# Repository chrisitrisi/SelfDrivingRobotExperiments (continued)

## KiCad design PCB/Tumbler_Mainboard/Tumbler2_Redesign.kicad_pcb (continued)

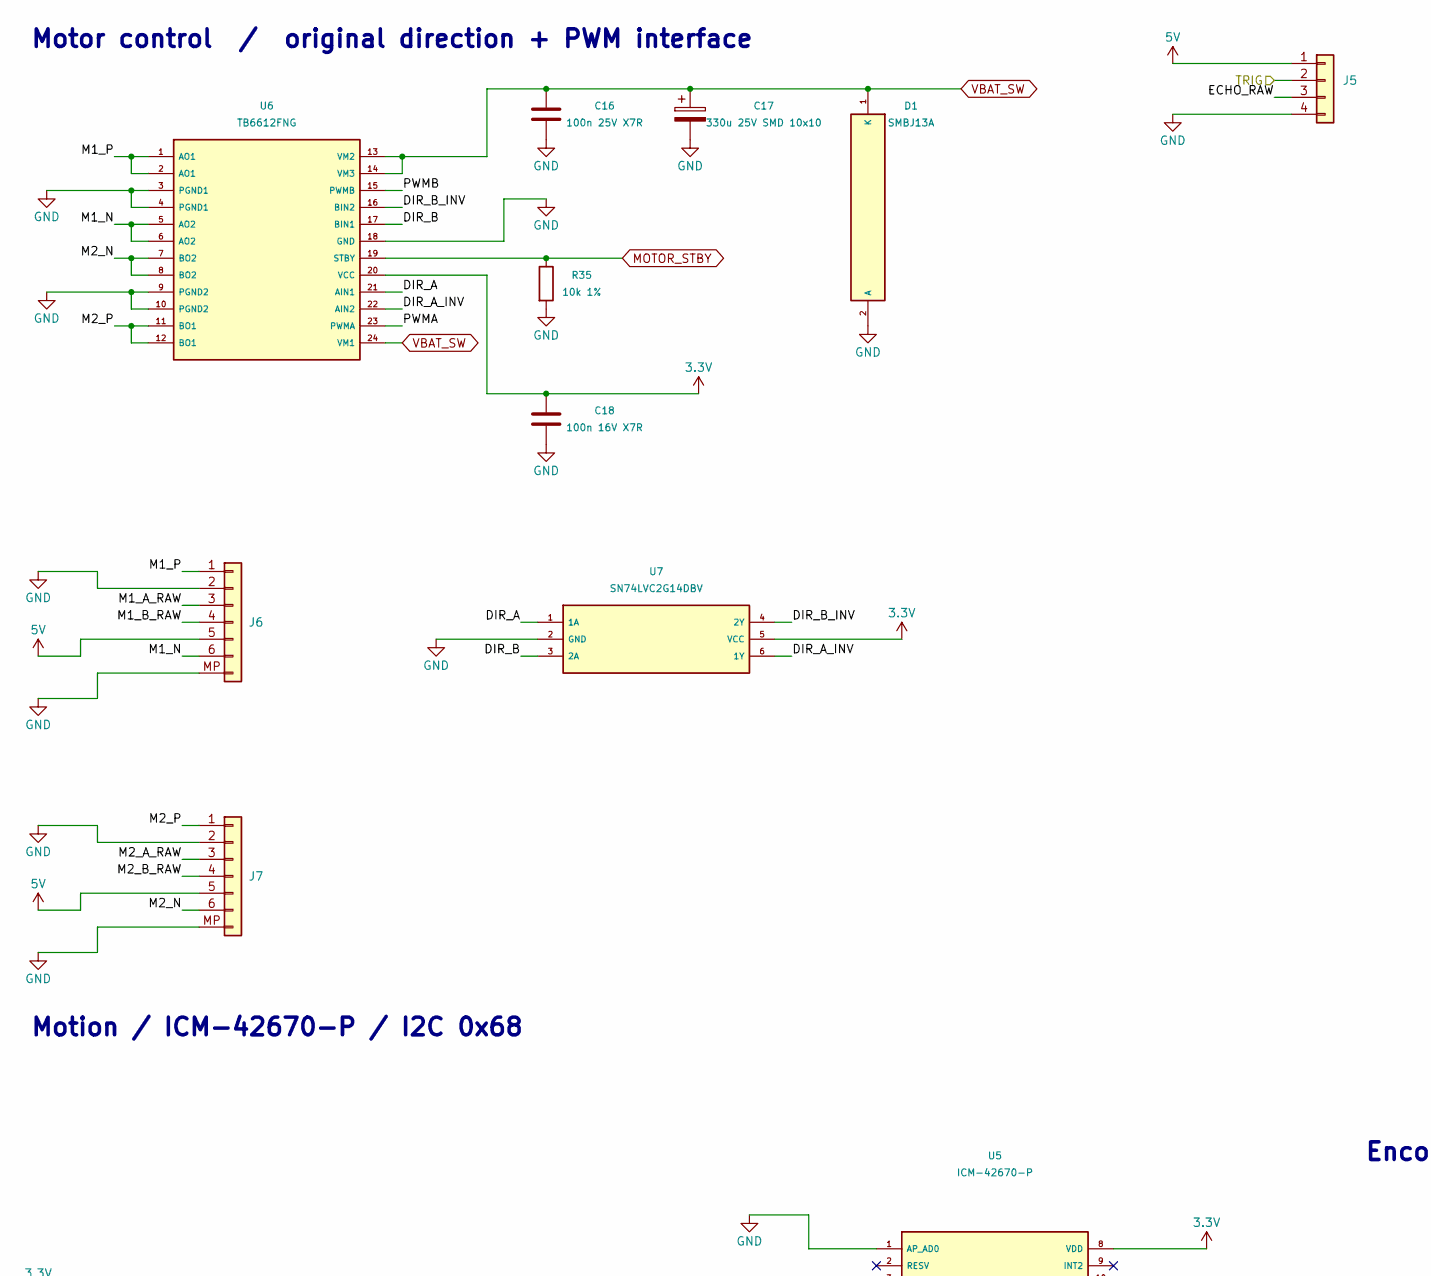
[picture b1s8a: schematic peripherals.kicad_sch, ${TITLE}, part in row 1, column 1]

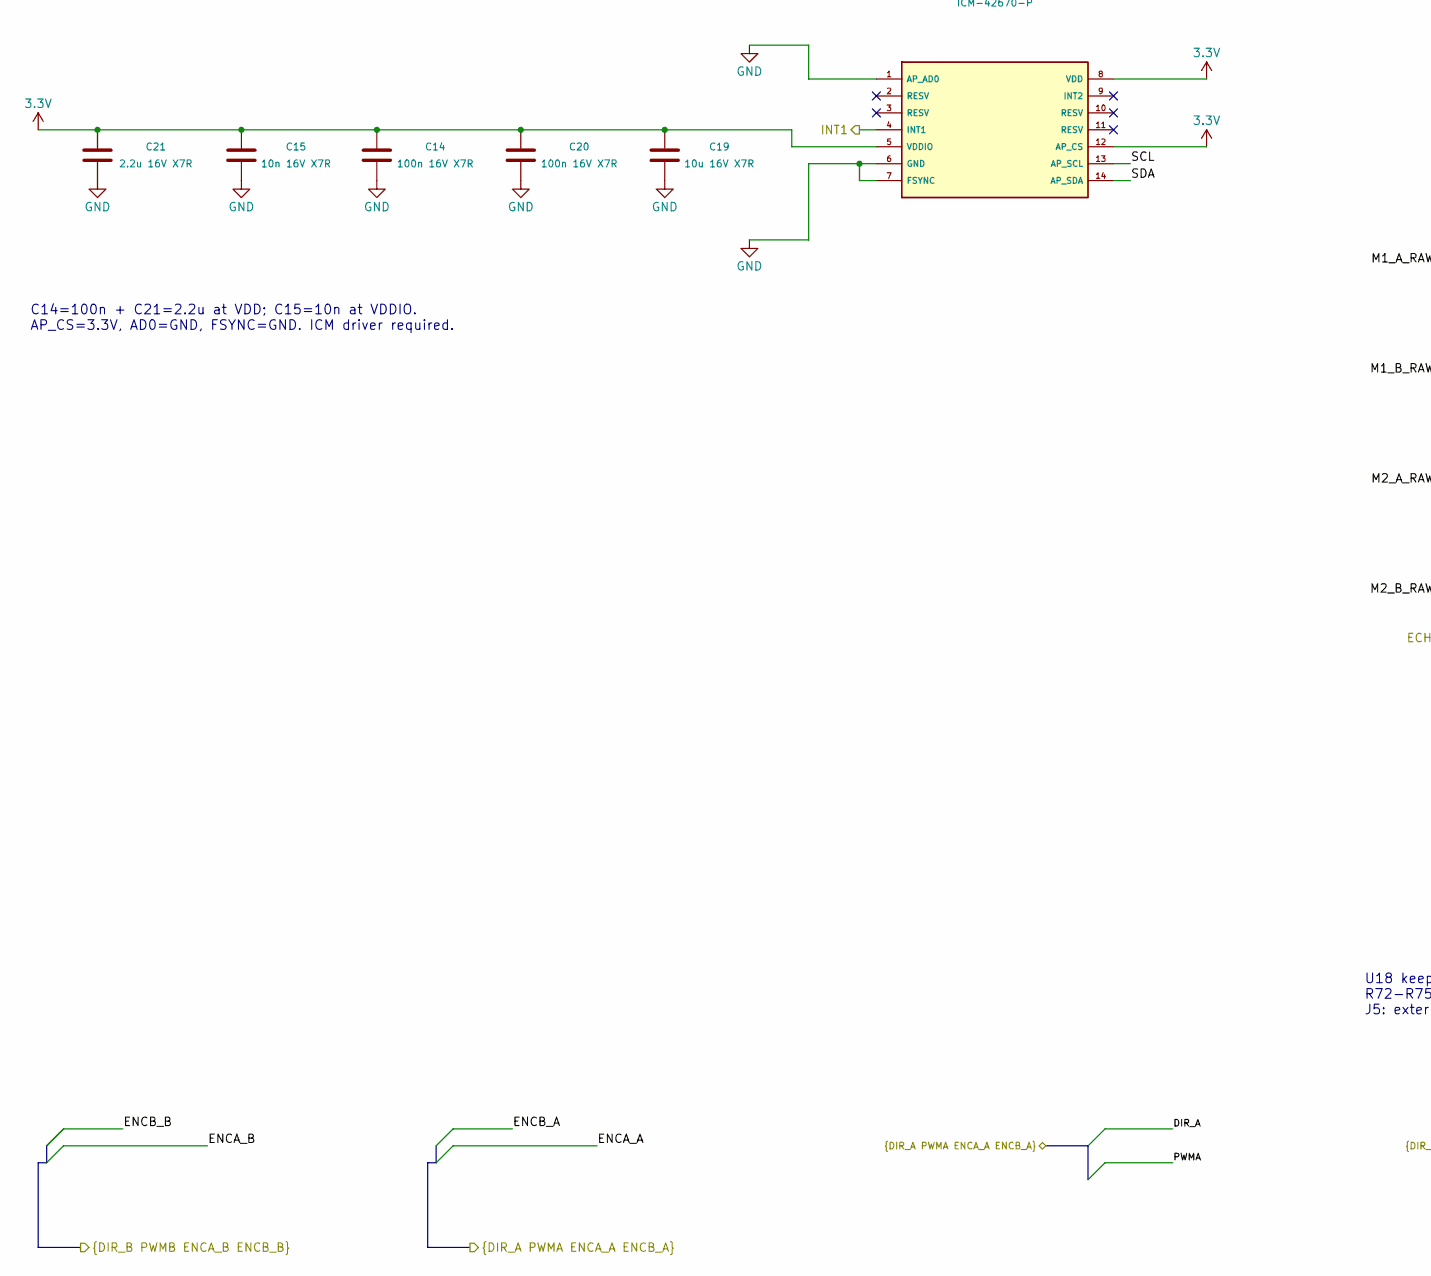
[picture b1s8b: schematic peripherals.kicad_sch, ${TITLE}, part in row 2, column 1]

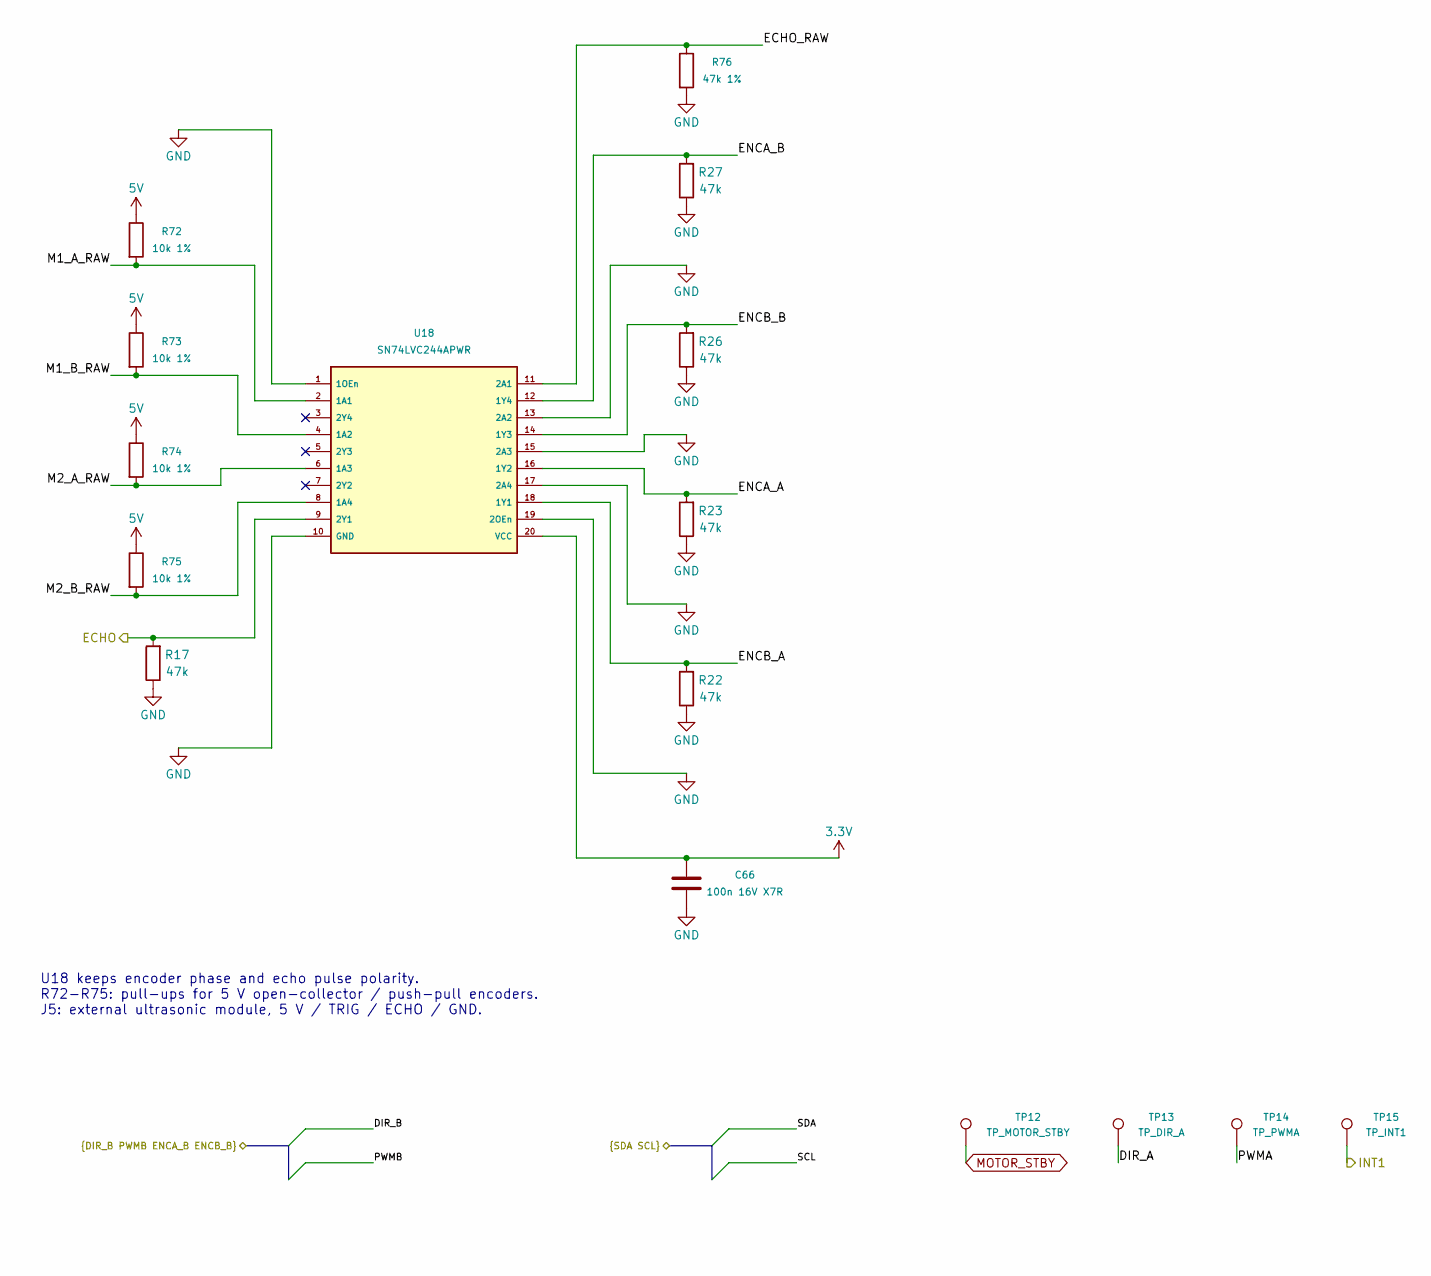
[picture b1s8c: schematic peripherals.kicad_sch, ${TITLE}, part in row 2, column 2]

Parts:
C14, C18, C20, C66: 100n 16V X7R; C_0603_1608Metric; LCSC PN C14663
C15: 10n 16V X7R; C_0603_1608Metric; LCSC PN C57112
C16: 100n 25V X7R; C_0603_1608Metric; LCSC PN C14663
C17: 330u 25V SMD 10x10; CP_Elec_10x10; LCSC PN C5632144
C19: 10u 16V X7R; C_0805_2012Metric; LCSC PN C95841
C21: 2.2u 16V X7R; C_0603_1608Metric; LCSC PN C6600149
D1: SMBJ13A; D_SMB; LCSC PN C353394
J5: Conn_01x04; PinHeader_1x04_P2.54mm_Vertical; LCSC PN C5116530
J6, J7: Conn_01x06; JST_XH_S6B-XH-SM4-TB_1x06-1MP_P2.50mm_Horizontal; LCSC PN C191914
R17, R22, R23, R26, R27: 47k; R_0603_1608Metric; LCSC PN C25819
R35, R72, R73, R74, R75: 10k 1%; R_0603_1608Metric; LCSC PN C25804
R76: 47k 1%; R_0603_1608Metric; LCSC PN C25819
TP12: TP_MOTOR_STBY; TestPoint_Pad_D1.0mm
TP13: TP_DIR_A; TestPoint_Pad_D1.0mm
TP14: TP_PWMA; TestPoint_Pad_D1.0mm
TP15: TP_INT1; TestPoint_Pad_D1.0mm
U5: ICM-42670-P; LGA-14_3x2.5mm_P0.5mm_LayoutBorder3x4y; LCSC PN C3288646
U6: TB6612FNG; SSOP-24_5.3x8.2mm_P0.65mm; LCSC PN C141517
U7: SN74LVC2G14DBV; SOT-23-6; LCSC PN C5375976
U18: SN74LVC244APWR; TSSOP-20_4.4x6.5mm_P0.65mm; LCSC PN C7668

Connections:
3.3V: C14.1, C15.1, C18.1, C19.1, C20.1, C21.1, C66.1, U5.5 (VDDIO), U5.8 (VDD), U5.12 (AP_CS), U6.20 (VCC), U7.5 (VCC), U18.20 (VCC); also elsewhere on the board
5V: J5.1, J6.5, J7.5, R72.1, R73.1, R74.1, R75.1; also elsewhere on the board
/LiDAR x8/SCL: U5.13 (AP_SCL); also elsewhere on the board
/LiDAR x8/SDA: U5.14 (AP_SDA); also elsewhere on the board
/MCU/DIR_A: TP13.1, U6.21 (AIN1), U7.1 (1A); also elsewhere on the board
/MCU/DIR_B: U6.17 (BIN1), U7.3 (2A); also elsewhere on the board
/MCU/ECHO: R17.2, U18.9 (2Y1); also elsewhere on the board
/MCU/ENCA_A: R23.2, U18.16 (1Y2); also elsewhere on the board
/MCU/ENCA_B: R27.2, U18.12 (1Y4); also elsewhere on the board
/MCU/ENCB_A: R22.2, U18.18 (1Y1); also elsewhere on the board
/MCU/ENCB_B: R26.2, U18.14 (1Y3); also elsewhere on the board
/MCU/INT1: TP15.1, U5.4 (INT1); also elsewhere on the board
/MCU/PWMA: TP14.1, U6.23 (PWMA); also elsewhere on the board
/MCU/PWMB: U6.15 (PWMB); also elsewhere on the board
/MCU/TRIG: J5.2; also elsewhere on the board
/Peripherals/DIR_A_INV: U6.22 (AIN2), U7.6 (1Y)
/Peripherals/DIR_B_INV: U6.16 (BIN2), U7.4 (2Y)
/Peripherals/ECHO_RAW: J5.3, R76.1, U18.11 (2A1)
/Peripherals/M1_A_RAW: J6.3, R72.2, U18.2 (1A1)
/Peripherals/M1_B_RAW: J6.4, R73.2, U18.4 (1A2)
/Peripherals/M1_N: J6.6, U6.5 (AO2), U6.6 (AO2)
/Peripherals/M1_P: J6.1, U6.1 (AO1), U6.2 (AO1)
/Peripherals/M2_A_RAW: J7.3, R74.2, U18.6 (1A3)
/Peripherals/M2_B_RAW: J7.4, R75.2, U18.8 (1A4)
/Peripherals/M2_N: J7.6, U6.7 (BO2), U6.8 (BO2)
/Peripherals/M2_P: J7.1, U6.11 (BO1), U6.12 (BO1)
GND: C14.2, C15.2, C16.2, C17.2, C18.2, C19.2, C20.2, C21.2, C66.2, D1.2 (A), J5.4, J6.2, J6.MP, J7.2, J7.MP, R17.1, R22.1, R23.1, R26.1, R27.1, R35.2, R76.2, U5.1 (AP_AD0), U5.6 (GND), U5.7 (FSYNC), U6.3 (PGND1), U6.4 (PGND1), U6.9 (PGND2), U6.10 (PGND2), U6.18 (GND), U7.2 (GND), U18.1 (1OEn), U18.10 (GND), U18.13 (2A2), U18.15 (2A3), U18.17 (2A4), U18.19 (2OEn); also elsewhere on the board
MOTOR_STBY: R35.1, TP12.1, U6.19 (STBY); also elsewhere on the board
VBAT_SW: C16.1, C17.1, D1.1 (K), U6.13 (VM2), U6.14 (VM3), U6.24 (VM1); also elsewhere on the board

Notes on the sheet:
Motor control / original direction + PWM interface
Encoder and echo inputs / 5 V to 3.3 V
Motion / ICM-42670-P / I2C 0x68
U18 keeps encoder phase and echo pulse polarity. R72-R75: pull-ups for 5 V open-collector / push-pull encoders. J5: external ultrasonic module, 5 V / TRIG / ECHO / GND.
C14=100n + C21=2.2u at VDD; C15=10n at VDDIO. AP_CS=3.3V, AD0=GND, FSYNC=GND. ICM driver required.

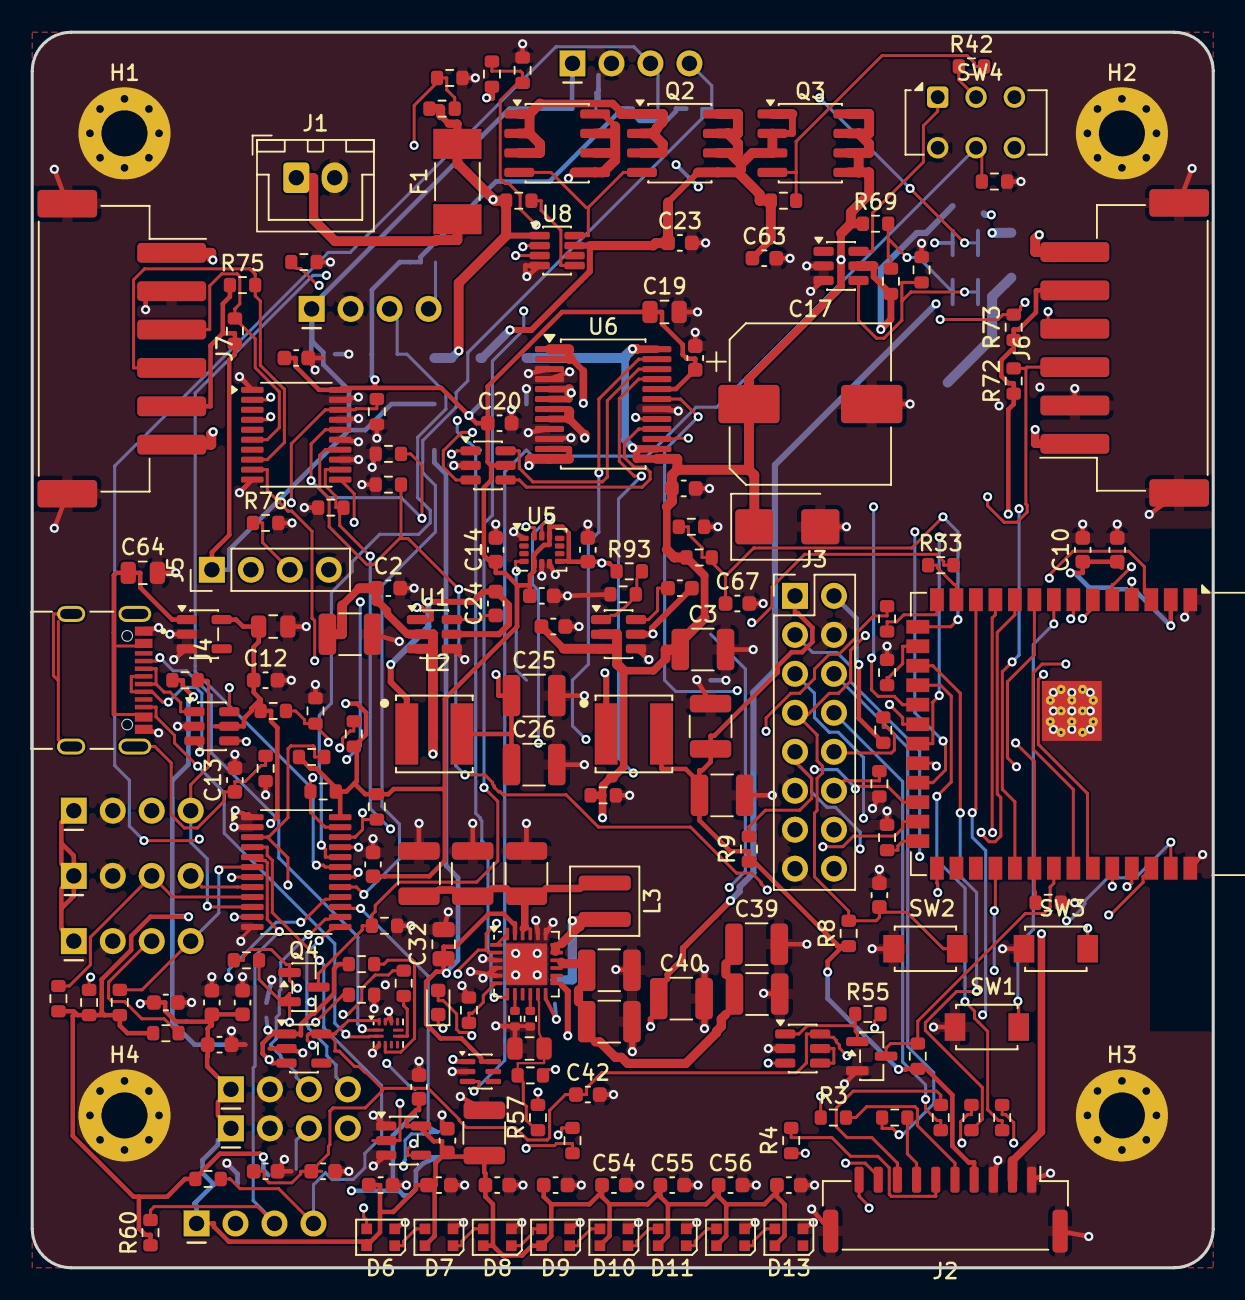
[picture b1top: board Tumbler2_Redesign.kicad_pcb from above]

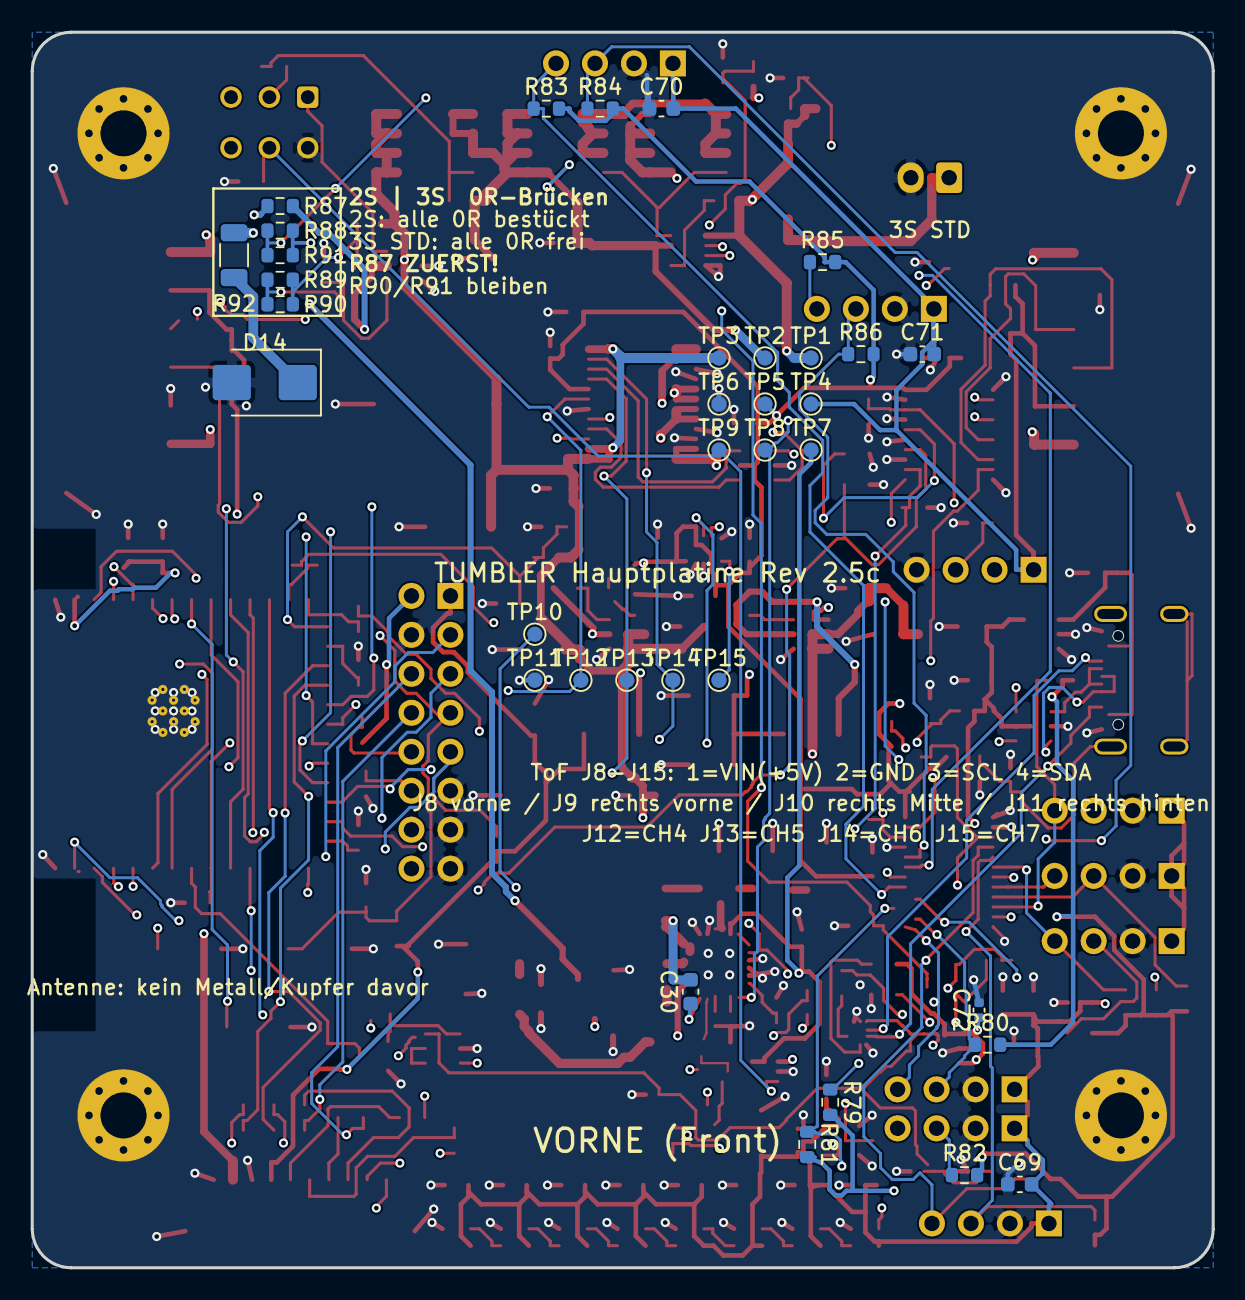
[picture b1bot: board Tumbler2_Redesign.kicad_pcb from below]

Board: 4 copper layers, 77.0 x 80.5 mm, 221 parts (35 on the bottom side), 133 nets.

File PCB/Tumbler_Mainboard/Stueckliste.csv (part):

Referenz;Wert / Bestelltyp;Footprint;Bestücken;Spezifikation / offene Freigabe;Datenblatt;LCSC (JLC, Stand 28.11.2026)
C1;22u 25V X7R;Capacitor_SMD:C_1210_3225Metric;Ja;"MLCC X7R; falls keine Spannung im Wert: >=16 V | Rev 2.5b: auf 22u/25V 1210 vereinheitlicht (eine JLC-Teilenummer weniger)";;C309062
C2;100n 25V X7R;Capacitor_SMD:C_0603_1608Metric;Ja;"MLCC X7R; falls keine Spannung im Wert: >=16 V";;C14663
C3;22u 25V X7R;Capacitor_SMD:C_1210_3225Metric;Ja;"MLCC X7R; falls keine Spannung im Wert: >=16 V | Rev 2.5b: auf 22u/25V 1210 vereinheitlicht (eine JLC-Teilenummer weniger)";;C309062
C4;100n 25V X7R;Capacitor_SMD:C_0603_1608Metric;Ja;"MLCC X7R; falls keine Spannung im Wert: >=16 V";;C14663
C6;22u 25V X7R;Capacitor_SMD:C_1210_3225Metric;Ja;"MLCC X7R; falls keine Spannung im Wert: >=16 V | Rev 2.5b: auf 22u/25V 1210 vereinheitlicht (eine JLC-Teilenummer weniger)";;C309062
C7;22u 25V X7R;Capacitor_SMD:C_1210_3225Metric;Ja;"MLCC X7R; falls keine Spannung im Wert: >=16 V | Rev 2.5b: auf 22u/25V 1210 vereinheitlicht (eine JLC-Teilenummer weniger)";;C309062
C8;100n 25V X7R;Capacitor_SMD:C_0603_1608Metric;Ja;"MLCC X7R; falls keine Spannung im Wert: >=16 V";;C14663
C9;10u 25V X5R;Capacitor_SMD:C_0603_1608Metric;Ja;MLCC X5R, 25 V, an 3,3 V;;C96446
C10;100nF;Capacitor_SMD:C_0603_1608Metric;Ja;"MLCC X7R; falls keine Spannung im Wert: >=16 V";;C14663
C11;1uF;Capacitor_SMD:C_0603_1608Metric;Ja;"MLCC X7R; falls keine Spannung im Wert: >=16 V";;C59782
C12;100nF;Capacitor_SMD:C_0603_1608Metric;Ja;"MLCC X7R; falls keine Spannung im Wert: >=16 V";;C14663
C13;100nF;Capacitor_SMD:C_0603_1608Metric;Ja;"MLCC X7R; falls keine Spannung im Wert: >=16 V";;C14663
C14;100n 16V X7R;Capacitor_SMD:C_0603_1608Metric;Ja;"MLCC X7R; falls keine Spannung im Wert: >=16 V";;C14663
C15;10n 16V X7R;Capacitor_SMD:C_0603_1608Metric;Ja;"MLCC X7R; falls keine Spannung im Wert: >=16 V";;C57112
C16;100n 25V X7R;Capacitor_SMD:C_0603_1608Metric;Ja;"MLCC X7R; falls keine Spannung im Wert: >=16 V";;C14663
C17;330u 25V SMD 10x10;Capacitor_SMD:CP_Elec_10x10;Ja;Rev 2.5b: SamYoung CLU25V330M10*10 (330 uF/25 V, 10x10 SMD, bei JLC lagernd);;C5632144
C18;100n 16V X7R;Capacitor_SMD:C_0603_1608Metric;Ja;"MLCC X7R; falls keine Spannung im Wert: >=16 V";;C14663
C19;10u 16V X7R;Capacitor_SMD:C_0805_2012Metric;Ja;"MLCC X7R; falls keine Spannung im Wert: >=16 V";;C95841
C20;100n 16V X7R;Capacitor_SMD:C_0603_1608Metric;Ja;"MLCC X7R; falls keine Spannung im Wert: >=16 V";;C14663
C21;2.2u 16V X7R;Capacitor_SMD:C_0603_1608Metric;Ja;"MLCC X7R; falls keine Spannung im Wert: >=16 V";;C6600149
C23;100n 25V X7R;Capacitor_SMD:C_0603_1608Metric;Ja;"MLCC X7R; falls keine Spannung im Wert: >=16 V";;C14663
C24;100n 25V X7R;Capacitor_SMD:C_0603_1608Metric;Ja;"MLCC X7R; falls keine Spannung im Wert: >=16 V";;C14663
C25;22u 25V X7R;Capacitor_SMD:C_1210_3225Metric;Ja;"MLCC X7R; falls keine Spannung im Wert: >=16 V | Rev 2.5b: auf 22u/25V 1210 vereinheitlicht (eine JLC-Teilenummer weniger)";;C309062
C26;22u 25V X7R;Capacitor_SMD:C_1210_3225Metric;Ja;"MLCC X7R; falls keine Spannung im Wert: >=16 V | Rev 2.5b: auf 22u/25V 1210 vereinheitlicht (eine JLC-Teilenummer weniger)";;C309062
C27;2.2u 25V X7R;Capacitor_SMD:C_0805_2012Metric;Ja;"MLCC X7R; falls keine Spannung im Wert: >=16 V";;C19110
C28;1u 16V X7R;Capacitor_SMD:C_0603_1608Metric;Ja;"MLCC X7R; falls keine Spannung im Wert: >=16 V";;C59782
C29;100n 16V X7R;Capacitor_SMD:C_0603_1608Metric;Ja;"MLCC X7R; falls keine Spannung im Wert: >=16 V";;C14663
C30;47n 25V X7R;Capacitor_SMD:C_0603_1608Metric;Ja;"MLCC X7R; falls keine Spannung im Wert: >=16 V";;C1622
C31;4.7u 25V X7R;Capacitor_SMD:C_0805_2012Metric;Ja;"MLCC X7R; falls keine Spannung im Wert: >=16 V";;C98195
C32;2.2u 25V X7R;Capacitor_SMD:C_0805_2012Metric;Ja;"MLCC X7R; falls keine Spannung im Wert: >=16 V";;C19110
C33;22u 25V X7R;Capacitor_SMD:C_1210_3225Metric;Ja;"Murata GRM32ER71E226KE15L; effektive C unter DC-Bias verifizieren";;C309062
C34;22u 25V X7R;Capacitor_SMD:C_1210_3225Metric;Ja;"Murata GRM32ER71E226KE15L; effektive C unter DC-Bias verifizieren";;C309062
C35;22u 25V X7R;Capacitor_SMD:C_1210_3225Metric;Ja;"Murata GRM32ER71E226KE15L; effektive C unter DC-Bias verifizieren";;C309062
C36;22u 25V X7R;Capacitor_SMD:C_1210_3225Metric;Ja;"Murata GRM32ER71E226KE15L; effektive C unter DC-Bias verifizieren";;C309062
C37;22u 25V X7R;Capacitor_SMD:C_1210_3225Metric;Ja;"Murata GRM32ER71E226KE15L; effektive C unter DC-Bias verifizieren";;C309062
C38;22u 25V X7R;Capacitor_SMD:C_1210_3225Metric;Ja;"Murata GRM32ER71E226KE15L; effektive C unter DC-Bias verifizieren";;C309062
C39;22u 25V X7R;Capacitor_SMD:C_1210_3225Metric;Ja;"Murata GRM32ER71E226KE15L; effektive C unter DC-Bias verifizieren";;C309062
C40;22u 25V X7R;Capacitor_SMD:C_1210_3225Metric;Ja;"Murata GRM32ER71E226KE15L; effektive C unter DC-Bias verifizieren";;C309062
C41;100n 16V X7R;Capacitor_SMD:C_0603_1608Metric;Ja;"MLCC X7R; falls keine Spannung im Wert: >=16 V";;C14663
C42;100n 16V X7R;Capacitor_SMD:C_0603_1608Metric;Ja;"MLCC X7R; falls keine Spannung im Wert: >=16 V";;C14663
C50;100nF;Capacitor_SMD:C_0603_1608Metric;Ja;"MLCC X7R; falls keine Spannung im Wert: >=16 V";;C14663
C51;100nF;Capacitor_SMD:C_0603_1608Metric;Ja;"MLCC X7R; falls keine Spannung im Wert: >=16 V";;C14663
C52;100nF;Capacitor_SMD:C_0603_1608Metric;Ja;"MLCC X7R; falls keine Spannung im Wert: >=16 V";;C14663
C53;100nF;Capacitor_SMD:C_0603_1608Metric;Ja;"MLCC X7R; falls keine Spannung im Wert: >=16 V";;C14663
C54;100nF;Capacitor_SMD:C_0603_1608Metric;Ja;"MLCC X7R; falls keine Spannung im Wert: >=16 V";;C14663
C55;100nF;Capacitor_SMD:C_0603_1608Metric;Ja;"MLCC X7R; falls keine Spannung im Wert: >=16 V";;C14663
C56;100nF;Capacitor_SMD:C_0603_1608Metric;Ja;"MLCC X7R; falls keine Spannung im Wert: >=16 V";;C14663
C57;100nF;Capacitor_SMD:C_0603_1608Metric;Ja;"MLCC X7R; falls keine Spannung im Wert: >=16 V";;C14663
C58;100n 16V X7R;Capacitor_SMD:C_0603_1608Metric;Ja;"X7R; Mindestspannung laut Wert; wirksame Kapazität unter DC-Bias prüfen";;C14663
C59;1u 16V X7R;Capacitor_SMD:C_0603_1608Metric;Ja;Abblockung +5V am ToF-Kabelanschluss;;C59782
C60;1u 16V X7R;Capacitor_SMD:C_0603_1608Metric;Ja;Abblockung +5V am ToF-Kabelanschluss;;C59782
C61;1u 16V X7R;Capacitor_SMD:C_0603_1608Metric;Ja;Abblockung +5V am ToF-Kabelanschluss;;C59782
C62;1u 16V X7R;Capacitor_SMD:C_0603_1608Metric;Ja;Abblockung +5V am ToF-Kabelanschluss;;C59782
C63;100n 25V X7R;Capacitor_SMD:C_0603_1608Metric;Ja;Rev 2.5: 25 V (PACK_SAFE bis 12,6 V bei 3S);;C14663
C64;2.2u 25V X7R;Capacitor_SMD:C_0805_2012Metric;Ja;"X7R; Mindestspannung laut Wert; wirksame Kapazität unter DC-Bias prüfen";;C19110
C65;22u 25V X7R;Capacitor_SMD:C_1210_3225Metric;Ja;"X7R; Mindestspannung laut Wert; wirksame Kapazität unter DC-Bias prüfen | Rev 2.5b: auf 22u/25V 1210 vereinheitlicht (eine JLC-Teilenummer weniger)";;C309062
C66;100n 16V X7R;Capacitor_SMD:C_0603_1608Metric;Ja;"X7R; Mindestspannung laut Wert; wirksame Kapazität unter DC-Bias prüfen";;C14663
C67;100n 16V X7R;Capacitor_SMD:C_0603_1608Metric;Ja;ADC-Puffer an BAT_ADC/IO3;;C14663
C68;1u 16V X7R;Capacitor_SMD:C_0603_1608Metric;Ja;Abblockung +5V an J12 (CH4);;C59782
C69;1u 16V X7R;Capacitor_SMD:C_0603_1608Metric;Ja;Abblockung +5V an J13 (CH5), Unterseite;;C59782
C70;1u 16V X7R;Capacitor_SMD:C_0603_1608Metric;Ja;Abblockung +5V an J14 (CH6), Unterseite;;C59782
C71;1u 16V X7R;Capacitor_SMD:C_0603_1608Metric;Ja;Abblockung +5V an J15 (CH7), Unterseite;;C59782
C72;1u 25V X5R;Capacitor_SMD:C_0402_1005Metric;Ja;Rev 2.5b: Eingangskondensator direkt an U9 VIN (Unterseite);;C52923
D1;SMBJ13A;Diode_SMD:D_SMB;Ja;"Rev 2.5: TVS an VBAT_SW, VRWM 13 V (3S 12,6 V), VBR 14,4–15,9 V, VC 21,5 V; immer bestückt";https://www.littelfuse.com/products/tvs-diodes/surface-mount/smbj;C353394
D2;CHG rot;LED_SMD:LED_0603_1608Metric;Ja;Rev 2.5b: rote Basic-LED KT-0603R statt amber;;C2286
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
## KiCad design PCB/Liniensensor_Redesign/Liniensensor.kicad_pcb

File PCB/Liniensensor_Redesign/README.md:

# Tumbler Liniensensor - Layout R3 (2S und 3S)

Das gesamte ZIP entpacken und **Liniensensor.kicad_pro** in KiCad 9 oder neuer öffnen.
Alle Unterordner zusammenlassen.

**R3.1 (26.11.2026): Pinbelegung Q1/Q2 korrigiert.** Der BCX56 hat im SOT-89 **Pin 1 = Emitter, 2 = Kollektor, 3 = Basis** (NXP- und Diodes-Datenblatt). Das KiCad-Standardsymbol `Transistor_BJT:BCX56` ist fälschlich B-C-E belegt, dadurch lagen Basis und Emitter vertauscht auf dem Footprint (Sensor wäre ohne LED-Strom gewesen). Jetzt eigenes Symbol `Tumbler_Sensor:BCX56_ECB`; Q1/Q2 neu angeschlossen (Pad 1 → 47-Ω-Emitterwiderstand R1/R9, Pad 3 → Basisteiler). DRC 0, ERC nur die zwei bekannten Label-Hinweise, Schaltplan-Parität ohne Netzabweichung. Gerber/Bohrdaten neu.

**R3 (26.11.2026):** Läuft an 2S **und** 3S (VBAT_SW 6,0–12,6 V, Spitzen 13,5 V) ohne Umbau. Q1/Q2 jetzt BCX56-16 (SOT-89) statt BC817-40, Basisteiler R2/R3/R7/R8 470 Ω statt 1 kΩ. Details und Rechnung: `Hinweise.md`. Gerber, Bohrdaten, Ansichten und `Mechanik/Liniensensor.step` sind auf R3 aktualisiert (KiCad 10).

Noch nicht nachgezogen: `Montage_und_Layout.pdf` nennt als Versorgung noch „2S“ (Mechanik/Lochbild darin unverändert gültig). Der Unterordner `Liniensensor_Redesign/` ist eine ältere Kopie (Schaltung R1, BC817) und nicht der aktuelle Stand.

- `Liniensensor.kicad_pcb`: vollständig geroutete Sensorplatine, 76 × 32 mm.
- `Liniensensor.kicad_sch` / `Liniensensor.pdf`: Schaltplan.
- `Montage_und_Layout.pdf`: Lochbild, Höhenkette, Vorlauf zur Radachse, Montage und Erprobung.
- `Mechanik/`: bestückte PCB als STEP; Halter und Distanzscheiben als STL; editierbarer OpenSCAD-Entwurf.
- `Fertigung/`: Gerber, PTH-/NPTH-Bohrdateien und Bohrbericht für diesen Prototyp.
- `Stueckliste.csv` und `Hinweise.md`: Bauteile, elektrische Auslegung und Pinbelegung.
- `Ansichten/`: tatsächliche CAD-Ansichten.
- `Pruefung.txt`, `Layoutpruefung.json`, `ERC.json`, `DRC.json`: Prüfstand.
- `symbols/`, `footprints/`, `3dmodels/`, lokale Bibliothekstabellen: mitgelieferte Bibliotheken.
- `Lizenzen/`: KiCad-Bibliothekslizenzen und Quellen.

## Mechanische Startwerte

Optische Fläche 2 mm über dem Boden, Sensoren mit 0,5 mm Sitzabstand zur PCB löten.
Daraus nominal: PCB-Unterseite 8,5 mm und Oberseite 10,1 mm über Boden.
Der Halter liegt oben bei 19,1 mm; diese Anlagefläche muss im neuen Gehäuse vorgesehen werden.
Vorlauf als Start: 20 mm vor der vordersten Reifenkante, also L = Raddurchmesser/2 + 20 mm vor der Radachse.
20 mm Längsverstellung im Halter. Reifenfreiheit, Linienbreite und Gehäusepassung vor Bestellung prüfen.
Der Halter ist ein universeller Adapter, kein am vorhandenen Chassis vermessener Ersatz.

## Fertigung

FR4, 2 Lagen, 1,6 mm, 35 µm Kupfer, Lötstopp beidseitig. CNY70 unten, alle SMD-Bauteile oben.
Nicht versehentlich nur die Platine aus dem ZIP herauskopieren: Bibliotheken und 3D-Modelle gehören dazu.
Nach eigenen Änderungen Massefläche neu füllen und ERC/DRC ausführen; Gerber anschließend neu exportieren.
Elektrische Regelprüfung ohne Befund, keine Freigabe eines am Roboter erprobten Serienstands.

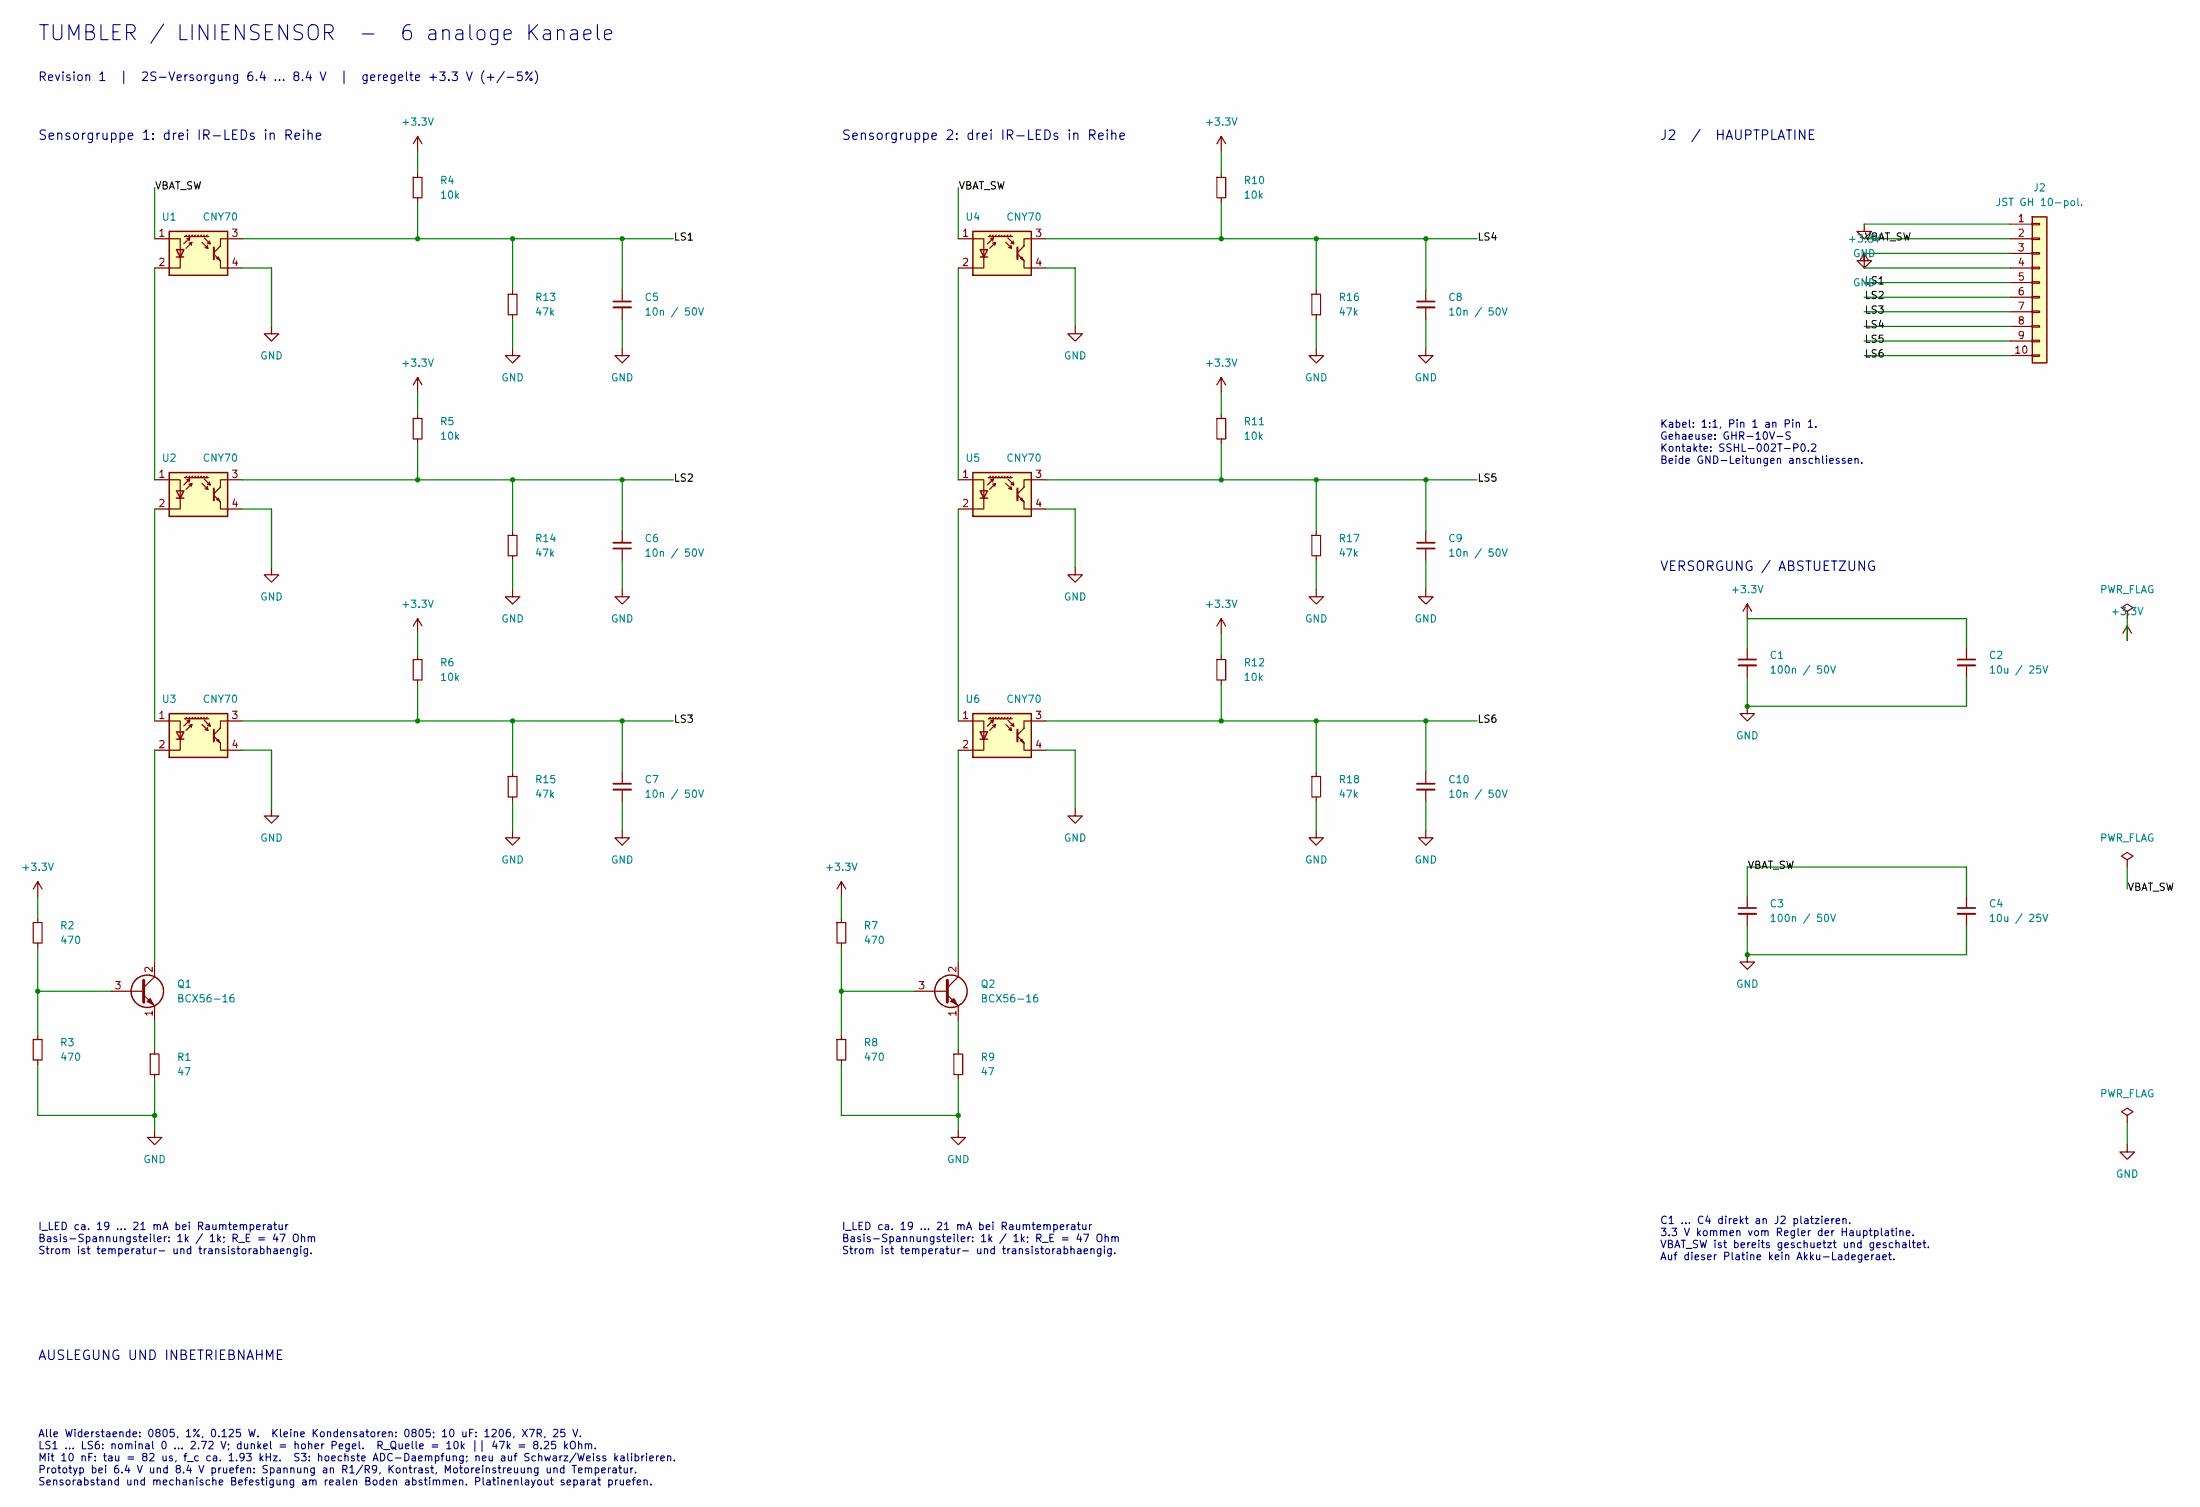
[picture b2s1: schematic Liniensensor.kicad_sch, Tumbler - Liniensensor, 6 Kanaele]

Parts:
C1, C3: 100n / 50V; C_0805_2012Metric; Rating 10%; X7R; 50 V; MPN C0805C104K5RACTU; LCSC PN C49678
C2, C4: 10u / 25V; C_1206_3216Metric; Rating 10%; X7R; 25 V; MPN C3216X7R1E106K160AB; LCSC PN C13585
C5, C6, C7, C8, C9, C10: 10n / 50V; C_0805_2012Metric; Rating 10%; X7R; 50 V; MPN C0805C103K5RACTU; LCSC PN C1710
J2: JST GH 10-pol.; JST_GH_SM10B-GHS-TB_1x10-1MP_P1.25mm_Horizontal; Rating 1.25 mm; 1 A with AWG26; 50 V; MPN SM10B-GHS-TB(LF)(SN); LCSC PN C2683602
Q1, Q2: BCX56-16; SOT-89-3; Rating 80 V; 1 A; Rth(j-a) 250 K/W min. Pad, 1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; MPN BCX5616QTA; LCSC PN C100026
R1, R9: 47; R_0805_2012Metric; Rating 1%; 0.125 W (standard mode, P70); MPN CRCW080547R0FKEA; LCSC PN C17714
R2, R3, R7, R8: 470; R_0805_2012Metric; Rating 1%; 0.125 W (standard mode, P70); MPN CRCW0805470RFKEA; LCSC PN C17710
R4, R5, R6, R10, R11, R12: 10k; R_0805_2012Metric; Rating 1%; 0.125 W (standard mode, P70); MPN CRCW080510K0FKEA; LCSC PN C17414
R13, R14, R15, R16, R17, R18: 47k; R_0805_2012Metric; Rating 1%; 0.125 W (standard mode, P70); MPN CRCW080547K0FKEA; LCSC PN C17713
U1, U2, U3, U4, U5, U6: CNY70; Vishay_CNY70; Rating IF design ~20 mA; absolute maximum 50 mA; MPN CNY70; LCSC PN C145423

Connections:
+3.3V: C1.1, C2.1, J2.4, R2.1, R4.1, R5.1, R6.1, R7.1, R10.1, R11.1, R12.1
/LS1: C5.1, J2.5, R4.2, R13.1, U1.3 (C)
/LS2: C6.1, J2.6, R5.2, R14.1, U2.3 (C)
/LS3: C7.1, J2.7, R6.2, R15.1, U3.3 (C)
/LS4: C8.1, J2.8, R10.2, R16.1, U4.3 (C)
/LS5: C9.1, J2.9, R11.2, R17.1, U5.3 (C)
/LS6: C10.1, J2.10, R12.2, R18.1, U6.3 (C)
/VBAT_SW: C3.1, C4.1, J2.2, U1.1 (A), U4.1 (A)
GND: C1.2, C2.2, C3.2, C4.2, C5.2, C6.2, C7.2, C8.2, C9.2, C10.2, J2.1, J2.3, R1.2, R3.2, R8.2, R9.2, R13.2, R14.2, R15.2, R16.2, R17.2, R18.2, U1.4 (E), U2.4 (E), U3.4 (E), U4.4 (E), U5.4 (E), U6.4 (E)
unnamed: Q1.3 (B), R2.2, R3.1
unnamed: Q1.2 (C), U3.2 (K)
unnamed: Q1.1 (E), R1.1
unnamed: Q2.3 (B), R7.2, R8.1
unnamed: Q2.2 (C), U6.2 (K)
unnamed: Q2.1 (E), R9.1
unnamed: U1.2 (K), U2.1 (A)
unnamed: U2.2 (K), U3.1 (A)
unnamed: U4.2 (K), U5.1 (A)
unnamed: U5.2 (K), U6.1 (A)

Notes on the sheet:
TUMBLER / LINIENSENSOR - 6 analoge Kanaele
Revision 1 | 2S-Versorgung 6.4 ... 8.4 V | geregelte +3.3 V (+/-5%)
Sensorgruppe 1: drei IR-LEDs in Reihe
I_LED ca. 19 ... 21 mA bei Raumtemperatur Basis-Spannungsteiler: 1k / 1k; R_E = 47 Ohm Strom ist temperatur- und transistorabhaengig.
Sensorgruppe 2: drei IR-LEDs in Reihe
J2 / HAUPTPLATINE
Kabel: 1:1, Pin 1 an Pin 1. Gehaeuse: GHR-10V-S Kontakte: SSHL-002T-P0.2 Beide GND-Leitungen anschliessen.
VERSORGUNG / ABSTUETZUNG
C1 ... C4 direkt an J2 platzieren. 3.3 V kommen vom Regler der Hauptplatine. VBAT_SW ist bereits geschuetzt und geschaltet. Auf dieser Platine kein Akku-Ladegeraet.
AUSLEGUNG UND INBETRIEBNAHME
Alle Widerstaende: 0805, 1%, 0.125 W. Kleine Kondensatoren: 0805; 10 uF: 1206, X7R, 25 V. LS1 ... LS6: nominal 0 ... 2.72 V; dunkel = hoher Pegel. R_Quelle = 10k || 47k = 8.25 kOhm. Mit 10 nF: tau = 82 us, f_c ca. 1.93 kHz. S3: hoechste ADC-Daempfung; neu auf Schwarz/Weiss kalibrieren. Prototyp bei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
